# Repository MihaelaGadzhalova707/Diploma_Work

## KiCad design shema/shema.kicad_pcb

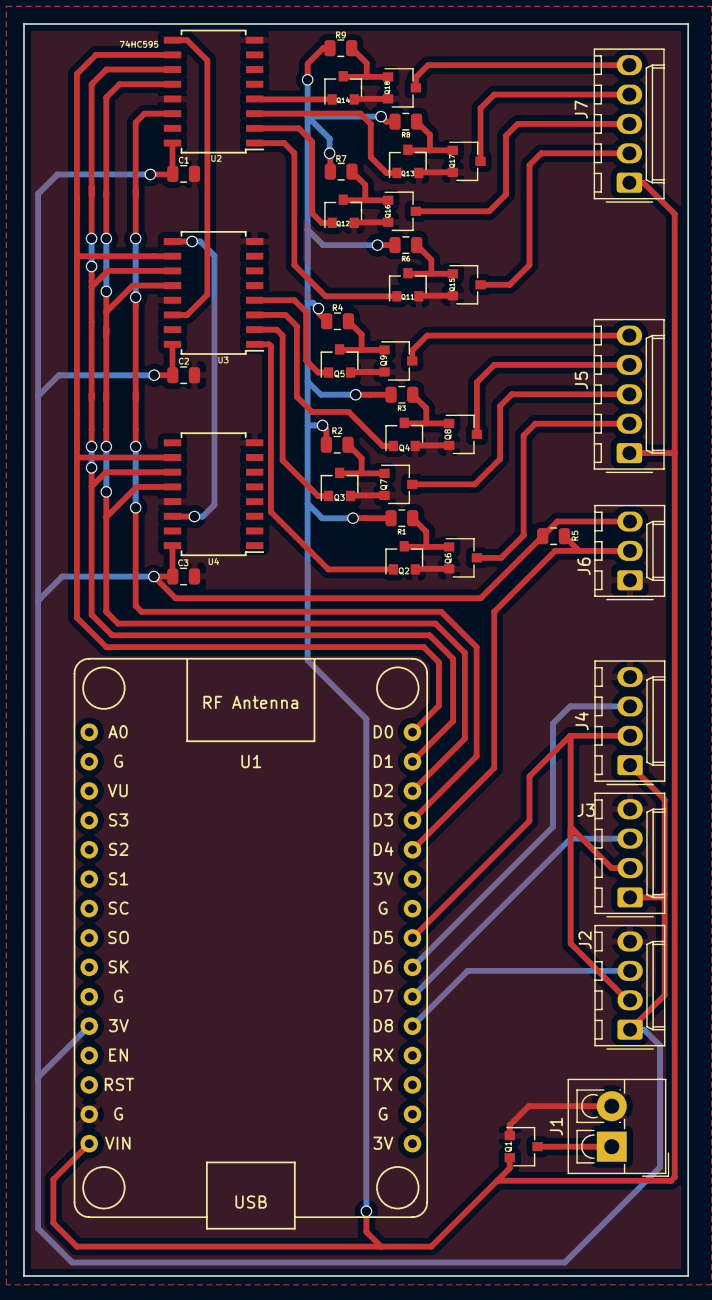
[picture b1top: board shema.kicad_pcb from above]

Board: 2 copper layers, 57.4 x 108.2 mm, 40 parts (0 on the bottom side), 39 nets.

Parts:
C1, C2, C3: 100nF; C_0805_2012Metric
J1: Power In; TerminalBlock_4Ucon_1x02_P3.50mm_Vertical
J2: US_01; Molex_KK-254_AE-6410-04A_1x04_P2.54mm_Vertical
J3: US_02; Molex_KK-254_AE-6410-04A_1x04_P2.54mm_Vertical
J4: US_03; Molex_KK-254_AE-6410-04A_1x04_P2.54mm_Vertical
J5: Valves; Molex_KK-254_AE-6410-05A_1x05_P2.54mm_Vertical
J6: Temp_Sensor; Molex_KK-254_AE-6410-03A_1x03_P2.54mm_Vertical
J7: Led_Strip; Molex_KK-254_AE-6410-05A_1x05_P2.54mm_Vertical
Q1: IRLML6402; SC-59
Q2, Q3, Q4, Q5, Q11, Q12, Q13, Q14: NPN; SOT-23
Q6, Q7, Q8, Q9, Q15, Q16, Q17, Q18: IRLML6344; SC-59
R1, R2, R3, R4, R6, R7, R8, R9: 1K; R_0805_2012Metric
R5: 4.7k; R_0805_2012Metric
U1: NodeMCU1.0(ESP-12E); NodeMCU1.0(12-E)
U2, U3, U4: 74HC595; SOIC-16W_5.3x10.2mm_P1.27mm

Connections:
+3V3: C1.1, C2.2, C3.1, J2.1, J3.1, J4.1, J6.3, R5.2, U1.11, U2.16, U3.16, U4.16
+12P: J1.1, Q1.3
+12V: J5.1, J7.1, Q1.2, R1.1, R2.1, R3.1, R4.1, R6.1, R7.1, R8.1, R9.1, U1.15
/Led_Blue: Q13.1, U2.3
/Led_Green: Q12.1, U2.2
/Led_Red: Q11.1, U2.1
/Led_White: Q14.1, U2.4
/Temp_sensor: J6.2, R5.1, U1.26
/Valve_01: Q2.1, U3.1
/Valve_02: Q3.1, U3.2
/Valve_03: Q4.1, U3.3
/Valve_04: Q5.1, U3.4
/us_01: J2.3, U1.20
/us_02: J3.3, U1.21
/us_03: J4.3, U1.22
/us_trig: J2.2, J3.2, J4.2, U1.23
GND: C1.2, C2.1, C3.2, J1.2, J2.4, J3.4, J4.4, J6.1, Q1.1, Q2.2, Q3.2, Q4.2, Q5.2, Q6.2, Q7.2, Q8.2, Q9.2, Q11.2, Q12.2, Q13.2, Q14.2, Q15.2, Q16.2, Q17.2, Q18.2, U1.14, U2.8, U2.13, U3.8, U3.13, U4.8, U4.13
unnamed: J5.2, Q6.3
unnamed: J5.3, Q7.3
unnamed: J5.4, Q8.3
unnamed: J5.5, Q9.3
unnamed: J7.2, Q15.3
unnamed: J7.3, Q16.3
unnamed: J7.4, Q17.3
unnamed: J7.5, Q18.3
unnamed: Q2.3, Q6.1, R1.2
unnamed: Q3.3, Q7.1, R2.2
unnamed: Q4.3, Q8.1, R3.2
unnamed: Q5.3, Q9.1, R4.2
unnamed: Q11.3, Q15.1, R6.2
unnamed: Q12.3, Q16.1, R7.2
unnamed: Q13.3, Q17.1, R8.2
unnamed: Q14.3, Q18.1, R9.2
unnamed: U1.27, U2.14
unnamed: U1.28, U2.12, U3.12, U4.12
unnamed: U1.29, U2.11, U3.11, U4.11
unnamed: U1.30, U2.10, U3.10, U4.10
unnamed: U2.9, U3.14
unnamed: U3.9, U4.14

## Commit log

2018-12-14 Led Strip Shema
2019-01-06 temperature_sensor
2019-01-06 mqtt
2019-01-06 mqtt_protocol
2019-01-06 wifi_manager_partly
2019-02-21 spine
2019-02-26 registration errors
2019-02-26 nex requests
2019-02-27 before deadline
2019-03-11 scheme
2019-03-11 footprints
2019-03-12 first steps
2019-03-13 trying smth
2019-03-16 temp sensor pcb
2019-03-21 second version
2019-03-25 ready
2019-03-25 fixed names
2019-03-31 arduino codes
2019-04-01 working temperature sensor
2019-04-01 working temp sensor
2019-04-17 arduino web server
2019-04-19 sensors, temp and led
2019-04-19 led_temp
2019-05-20 some code
2019-05-27 probably not finished
2019-05-30 presentation
2019-06-04 optimisation
2019-06-05 original code
2019-06-06 time
2019-10-29 Bump mongoose from 5.4.14 to 5.7.5 in /aqua
    Bumps [mongoose](https://github.com/Automattic/mongoose) from 5.4.14 to 5.7.5.
    - [Release notes](https://github.com/Automattic/mongoose/releases)
    - [Changelog](https://github.com/Automattic/mongoose/blob/master/History.md)
    - [Commits](https://github.com/Automattic/mongoose/compare/5.4.14...5.7.5)
2022-12-08 Bump qs and express in /aqua
    Bumps [qs](https://github.com/ljharb/qs) to 6.11.0 and updates ancestor dependency [express](https://github.com/expressjs/express). These dependencies need to be updated together.
    Updates `qs` from 6.5.2 to 6.11.0
    - [Release notes](https://github.com/ljharb/qs/releases)
    - [Changelog](https://github.com/ljharb/qs/blob/main/CHANGELOG.md)
    - [Commits](https://github.com/ljharb/qs/compare/v6.5.2...v6.11.0)
    Updates `express` from 4.16.4 to 4.18.2
2022-12-09 Bump express from 4.16.4 to 4.17.3 in /aqua
    Bumps [express](https://github.com/expressjs/express) from 4.16.4 to 4.17.3.
    - [Release notes](https://github.com/expressjs/express/releases)
    - [Changelog](https://github.com/expressjs/express/blob/master/History.md)
    - [Commits](https://github.com/expressjs/express/compare/4.16.4...4.17.3)
    ---
    updated-dependencies:
